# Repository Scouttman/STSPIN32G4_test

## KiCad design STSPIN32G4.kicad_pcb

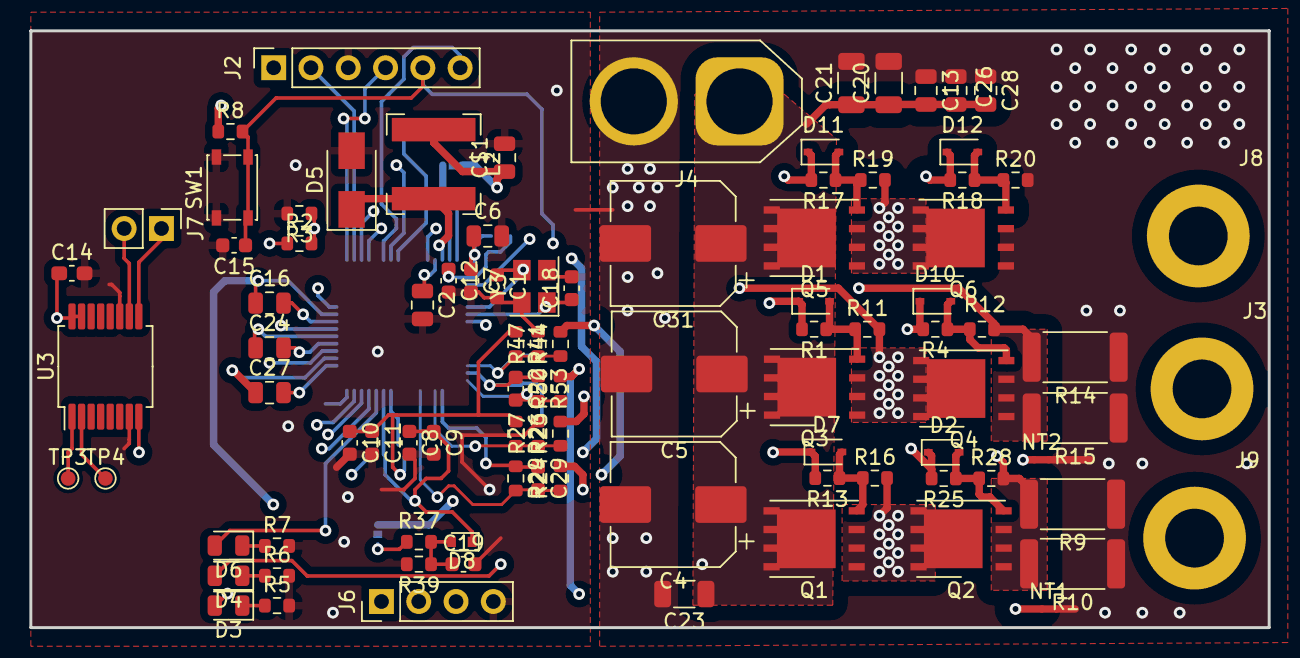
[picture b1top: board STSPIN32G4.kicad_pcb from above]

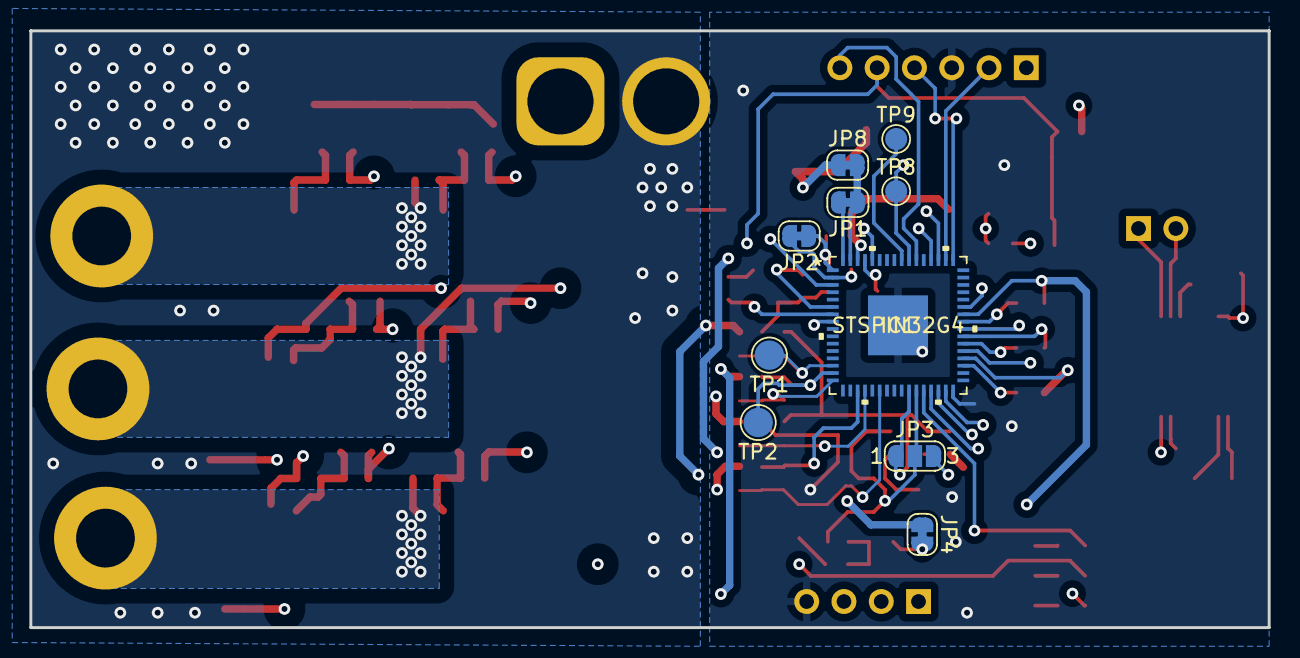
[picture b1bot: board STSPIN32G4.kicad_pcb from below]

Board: 4 copper layers, 84.3 x 40.6 mm, 104 parts (10 on the bottom side), 58 nets.

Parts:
C1, C18: 20p; C_0603_1608Metric
C2, C13, C26, C28: 220nF; C_0805_2012Metric
C4, C5, C31: 220uF; CP_Elec_8x10
C6: 10uF; C_0805_2012Metric
C7, C9, C11, C12, C15: 100nF; C_0603_1608Metric
C8, C10: 1uF; C_0603_1608Metric
C14: 0.1uF; C_0603_1608Metric_Pad1.08x0.95mm_HandSolder
C16, C24, C27: 1uF; C_0805_2012Metric
C19: 33nf; C_0603_1608Metric
C20, C21, C23: 2.2uf; C_1206_3216Metric
C22, C29: N.M; C_0603_1608Metric
C$1: 10uf 25v; C_0805_2012Metric
D1, D2, D7, D10, D11, D12: 1N4148WS; D_SOD-323
D3, D4, D6: LED; LED_0805_2012Metric
D5: SS210; D_SMA
D8: BAT30k; D_SOD-523
IC1: STSPIN32G4
J2: Conn_01x06_Male; PinSocket_1x06_P2.54mm_Vertical
J3, J8, J9: Conn_01x01; connector_wire_esc
J4: Conn_01x02_Female; AMASS_XT60-F_1x02_P7.20mm_Vertical
J6: Conn_01x04_Female; PinHeader_1x04_P2.54mm_Vertical
J7: Conn_01x02; PinHeader_1x02_P2.54mm_Vertical
JP1, JP2, JP4, JP8: Jumper_2_Bridged; SolderJumper-2_P1.3mm_Bridged_RoundedPad1.0x1.5mm
JP3: Jumper_NC_Dual; SolderJumper-3_P1.3mm_Open_RoundedPad1.0x1.5mm_NumberLabels
L2: 18uh; L_Bourns-SRN6028
NT1, NT2: NetTie_2; NetTie-2_SMD_Pad0.5mm
Q1, Q2, Q3, Q4, Q5, Q6: Q_NMOS_GDS; DFN-8-1EP_6x5mm_P1.27mm_EP4x4mm
R1, R4, R13, R17, R18, R25: 33; R_0603_1608Metric
R2, R26, R27, R41, R47: 22k; R_0603_1608Metric
R3: 10k; R_0603_1608Metric
R5, R6, R7: 220; R_0603_1608Metric
R8: 100k; R_0603_1608Metric
R9, R10, R14, R15: 4mΩ; R_2512_6332Metric
R11, R12, R16, R19, R20, R28: N.M.; R_0603_1608Metric
R23, R24, R44, R50: 1.5k; R_0603_1608Metric
R29, R53: 11k; R_0603_1608Metric
R37: 72.3k; R_0603_1608Metric
R39: 3.01k; R_0603_1608Metric
SW1: SW_MEC_5G; SW_SPST_PTS810
TP1, TP2: TestPoint; TestPoint_Pad_D2.0mm
TP3, TP4: TestPoint; TestPoint_Pad_D1.0mm
TP8, TP9: TestPoint; TestPoint_Pad_D1.5mm
U3: AS5045B; SSOP-16_5.3x6.2mm_P0.65mm
Y3: 24mhz; Crystal_SMD_3225-4Pin_3.2x2.5mm

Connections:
BOOT1: C16.2, IC1.41 (BOOT1)
BOOT2: C24.2, IC1.38 (BOOT2)
BOOT3: C27.2, IC1.35 (BOOT3)
GHS1: D7.1 (K), IC1.43 (GHS1), R13.2
GHS2: D1.1 (K), IC1.40 (GHS2), R1.2
GHS3: D11.1 (K), IC1.37 (GHS3), R17.2
GLS1: D2.1 (K), IC1.29 (GLS1), R25.2
GLS2: D10.1 (K), IC1.30 (GLS2), R4.2
GLS3: D12.1 (K), IC1.31 (GLS3), R18.2
GND: C1.2, C2.2, C4.2, C5.2, C6.2, C7.2, C8.2, C9.2, C10.2, C11.2, C12.2, C13.1, C14.2, C15.2, C18.2, C19.2, C20.2, C21.2, C23.2, C26.1, C28.1, C31.2, C$1.2, D5.2 (A), IC1.32 (PGND), IC1.65 (VSS), J2.3, J4.2, J6.4, NT1.2, NT2.2, Q6.3 (S), R3.2, R5.2, R6.2, R7.2, R9.1, R10.1, R14.1, R15.1, R20.2, R27.2, R39.2, R47.2, SW1.1, U3.7 (VSS), U3.11 (CSn), Y3.2, Y3.4
I2C1_SCL: IC1.51 (PA15), J6.1
I2C1_SDA: IC1.60 (PB9), J6.2
unnamed: D1.2 (A), Q3.1 (G), R1.1, R11.1
unnamed: D2.2 (A), Q2.1 (G), R25.1, R28.1
unnamed: D3.1 (K), R5.1
unnamed: D4.1 (K), R6.1
unnamed: D6.1 (K), R7.1
unnamed: D7.2 (A), Q1.1 (G), R13.1, R16.1
unnamed: D10.2 (A), Q4.1 (G), R4.1, R12.1
unnamed: D11.2 (A), Q5.1 (G), R17.1, R19.1
unnamed: D12.2 (A), Q6.1 (G), R18.1, R20.1
unnamed: C2.1, IC1.61 (VM), JP4.1 (A)
unnamed: C$1.1, JP8.1 (A), L2.2
unnamed: TP4.1, U3.2 (MagDECn)
unnamed: TP3.1, U3.1 (MagINCn)
OPN1: C22.2, IC1.16 (PA3), R50.1, R53.2
OPN2: C29.2, IC1.22 (PC5), R24.1, R29.2
OPO1: C22.1, IC1.15 (PA2), R53.1, TP2.1
OPO2: C29.1, IC1.19 (PA6), R29.1
OPP1: IC1.14 (PA1), R41.2, R44.1, R47.1, TP1.1
OPP2: IC1.20 (PA7), R23.1, R26.2, R27.1
OSC_IN: C1.1, IC1.6 (PF0), Y3.3
OSC_OUT: C18.1, IC1.7 (PF1), Y3.1
OUT1: C16.1, IC1.42 (OUT1), J9.1, Q1.3 (S), Q2.2 (D), R16.2
OUT2: C24.1, IC1.39 (OUT2), J3.1, Q3.3 (S), Q4.2 (D), R11.2
OUT3: C27.1, IC1.36 (OUT3), J8.1, Q5.3 (S), Q6.2 (D), R19.2
PA0: C19.1, D8.2 (A), R37.2, R39.1
SCREF: IC1.52 (SCREF), R2.2, R3.1
SPI1_MISO: IC1.55 (PB4), J7.1, TP8.1, U3.9 (DO)
SPI1_MOSI: IC1.56 (PB5), TP9.1
SPI1_SCK: IC1.54 (PB3), J2.6, J7.2, U3.10 (CLK)
SW: D5.1 (K), IC1.62 (SW), L2.1
SWCLK: IC1.50 (PA14), J2.2
SWDIO: IC1.49 (PA13), J2.4
USER1: D4.2 (A), IC1.3 (PC13)
USER2: D6.2 (A), IC1.28 (PB10)
VBAT: C12.1, IC1.2 (VBAT), JP2.2 (B)
VCC: IC1.63 (VCC), JP1.1 (A), JP8.2 (B)
VDD: C6.1, C7.1, C14.1, D3.2 (A), IC1.1 (REG3V3/VDD), J2.1, J6.3, JP2.1 (A), JP3.3, R2.1, R8.1, U3.8 (PDIO), U3.15 (VDD3V3), U3.16 (VDD5V)
VDDA: C8.1, C9.1, D8.1 (K), IC1.27 (VDDA), JP3.2
VM: C4.1, C5.1, C13.2, C20.1, C21.1, C23.1, C26.2, C28.2, C31.1, J4.1, JP4.2 (B), Q1.2 (D), Q3.2 (D), Q5.2 (D), R37.1
VREF+: C10.1, C11.1, IC1.26 (VREF+), JP3.1, R26.1, R41.1
VREGIN: IC1.64 (REGIN), JP1.2 (B)
VSHUNT1N: NT1.1, R50.2
VSHUNT1P: Q2.3 (S), R9.2, R10.2, R28.2, R44.2
VSHUNT2N: NT2.1, R24.2
VSHUNT2P: Q4.3 (S), R12.2, R14.2, R15.2, R23.2
nRST: C15.1, IC1.8 (PG10), J2.5, R8.2, SW1.2

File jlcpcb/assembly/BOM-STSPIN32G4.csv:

Comment,Designator,Footprint,LCSC
100nF,"C11,C12,C14,C15,C7,C9",C_0603_1608Metric,C14663
SS210,D5,D_SMA,C14996
1uF,"C10,C8",C_0603_1608Metric,C15849
10uF,C6,C_0805_2012Metric,C15850
20p,"C1,C18",C_0603_1608Metric,C1648
Q_NMOS_GDS,"Q1,Q2,Q3,Q4,Q5,Q6",DFN-8-1EP_6x5mm_P1.27mm_EP4x4mm,C180959
33nf,C19,C_0603_1608Metric,C21117
1N4148WS,"D1,D10,D11,D12,D2,D7",D_SOD-323,C2128
1.5k,"R23,R24,R44,R50",R_0603_1608Metric,C22843
LED,D4,LED_0805_2012Metric,C2296
220,"R5,R6,R7",R_0603_1608Metric,C22962
LED,D3,LED_0805_2012Metric,C2297
33,"R1,R13,R17,R18,R25,R4",R_0603_1608Metric,C23140
100k,R8,R_0603_1608Metric,C25803
10k,R3,R_0603_1608Metric,C25804
11k,"R29,R53",R_0603_1608Metric,C25950
22k,"R2,R26,R27,R41,R47",R_0603_1608Metric,C27920
1uF,"C16,C24,C27",C_0805_2012Metric,C28323
SW_MEC_5G,SW1,SW_SPST_PTS810,C318938
LED,D6,LED_0805_2012Metric,C34499
4mΩ,"R10,R14,R15,R9",R_2512_6332Metric,C375693
AS5045B,U3,SSOP-16_5.3x6.2mm_P0.65mm,C415804
18uh,L2,L_Bourns-SRN6028,C467143
220nF,"C13,C2,C26,C28",C_0805_2012Metric,C5378
2.2uf,"C20,C21,C23",C_1206_3216Metric,C650969
220uF,"C31,C4,C5",CP_Elec_8x10,C72524
24mhz,Y3,Crystal_SMD_3225-4Pin_3.2x2.5mm,C9002
Conn_01x02_Female,J4,AMASS_XT60-F_1x02_P7.20mm_Vertical,
Conn_01x06_Male,J2,PinSocket_1x06_P2.54mm_Vertical,
Conn_01x04_Female,J6,PinHeader_1x04_P2.54mm_Vertical,
BAT30k,D8,D_SOD-523,
Jumper_2_Bridged,JP8,SolderJumper-2_P1.3mm_Bridged_RoundedPad1.0x1.5mm,
TestPoint,TP1,TestPoint_Pad_D2.0mm,
NetTie_2,NT1,NetTie-2_SMD_Pad0.5mm,
72.3k,R37,R_0603_1608Metric,
N.M,C22,C_0603_1608Metric,
3.01k,R39,R_0603_1608Metric,
Conn_01x01,J3,connector_wire_esc,
TestPoint,TP2,TestPoint_Pad_D2.0mm,
N.M.,R16,R_0603_1608Metric,
N.M.,R28,R_0603_1608Metric,
STSPIN32G4,IC1,STSPIN32G4,
Jumper_2_Bridged,JP2,SolderJumper-2_P1.3mm_Bridged_RoundedPad1.0x1.5mm,
Jumper_2_Bridged,JP4,SolderJumper-2_P1.3mm_Bridged_RoundedPad1.0x1.5mm,
Jumper_2_Bridged,JP1,SolderJumper-2_P1.3mm_Bridged_RoundedPad1.0x1.5mm,
Jumper_NC_Dual,JP3,SolderJumper-3_P1.3mm_Open_RoundedPad1.0x1.5mm_NumberLabels,
TestPoint,TP9,TestPoint_Pad_D1.5mm,
TestPoint,TP8,TestPoint_Pad_D1.5mm,
Conn_01x01,J8,connector_wire_esc,
Conn_01x01,J9,connector_wire_esc,
NetTie_2,NT2,NetTie-2_SMD_Pad0.5mm,
N.M.,R20,R_0603_1608Metric,
N.M.,R19,R_0603_1608Metric,
N.M.,R12,R_0603_1608Metric,
N.M.,R11,R_0603_1608Metric,
N.M,C29,C_0603_1608Metric,
Conn_01x02,J7,PinHeader_1x02_P2.54mm_Vertical,
TestPoint,TP4,TestPoint_Pad_D1.0mm,
TestPoint,TP3,TestPoint_Pad_D1.0mm,

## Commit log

2023-03-14 inital commit of hopefully needed core files
2023-03-14 added some missing sch
2023-06-03 Can't remember what these changes are
2023-07-28 revision 3
2023-07-28 delted output files
2023-07-28 jlc outputs

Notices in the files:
parts and their libraries:
Copyright 2021 Accelerated Designs. All rights reserved.
